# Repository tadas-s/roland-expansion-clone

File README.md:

# DIY Roland JV-1080 expansion card

Recently I restored a [Roland XP-60][1] synth for a friend. It's a digital sample
based synth with possibility of expanding sample set with up to 4 expansion
cards. And, while looking at service manual I got carried away a little...
Those expansion cards have a pretty straightforward interface - 8 bit data bus,
20 bit address bus, a few chip enable pins. Looked like something very DIYable.

Needless to say, I'm not the first one to notice it. Someone made copies of available
expansions and reverse engineered the format. [SRJV][3] is a script collection
to create/manipulate those ROMs.

# Schematic

For my own clone I used AM29F016D-70E4C flash chips. These are obsolete but still
widely available on eBay.

I included extra headers to expose flash WE, RESET for in-circuit programming,
but that part is untested - I ended up pre-programming chips before soldering.

# PCB

Did not want to spend too much time on layout so went with a more expensive
4 layer board.

# Assembled board

Two expansions installed next to one original from Roland:

[1]: https://www.vintagesynth.com/roland/xp-60
[2]: https://en.wikipedia.org/wiki/Roland_JV-1080
[3]: https://github.com/PythonBlue/SRJV

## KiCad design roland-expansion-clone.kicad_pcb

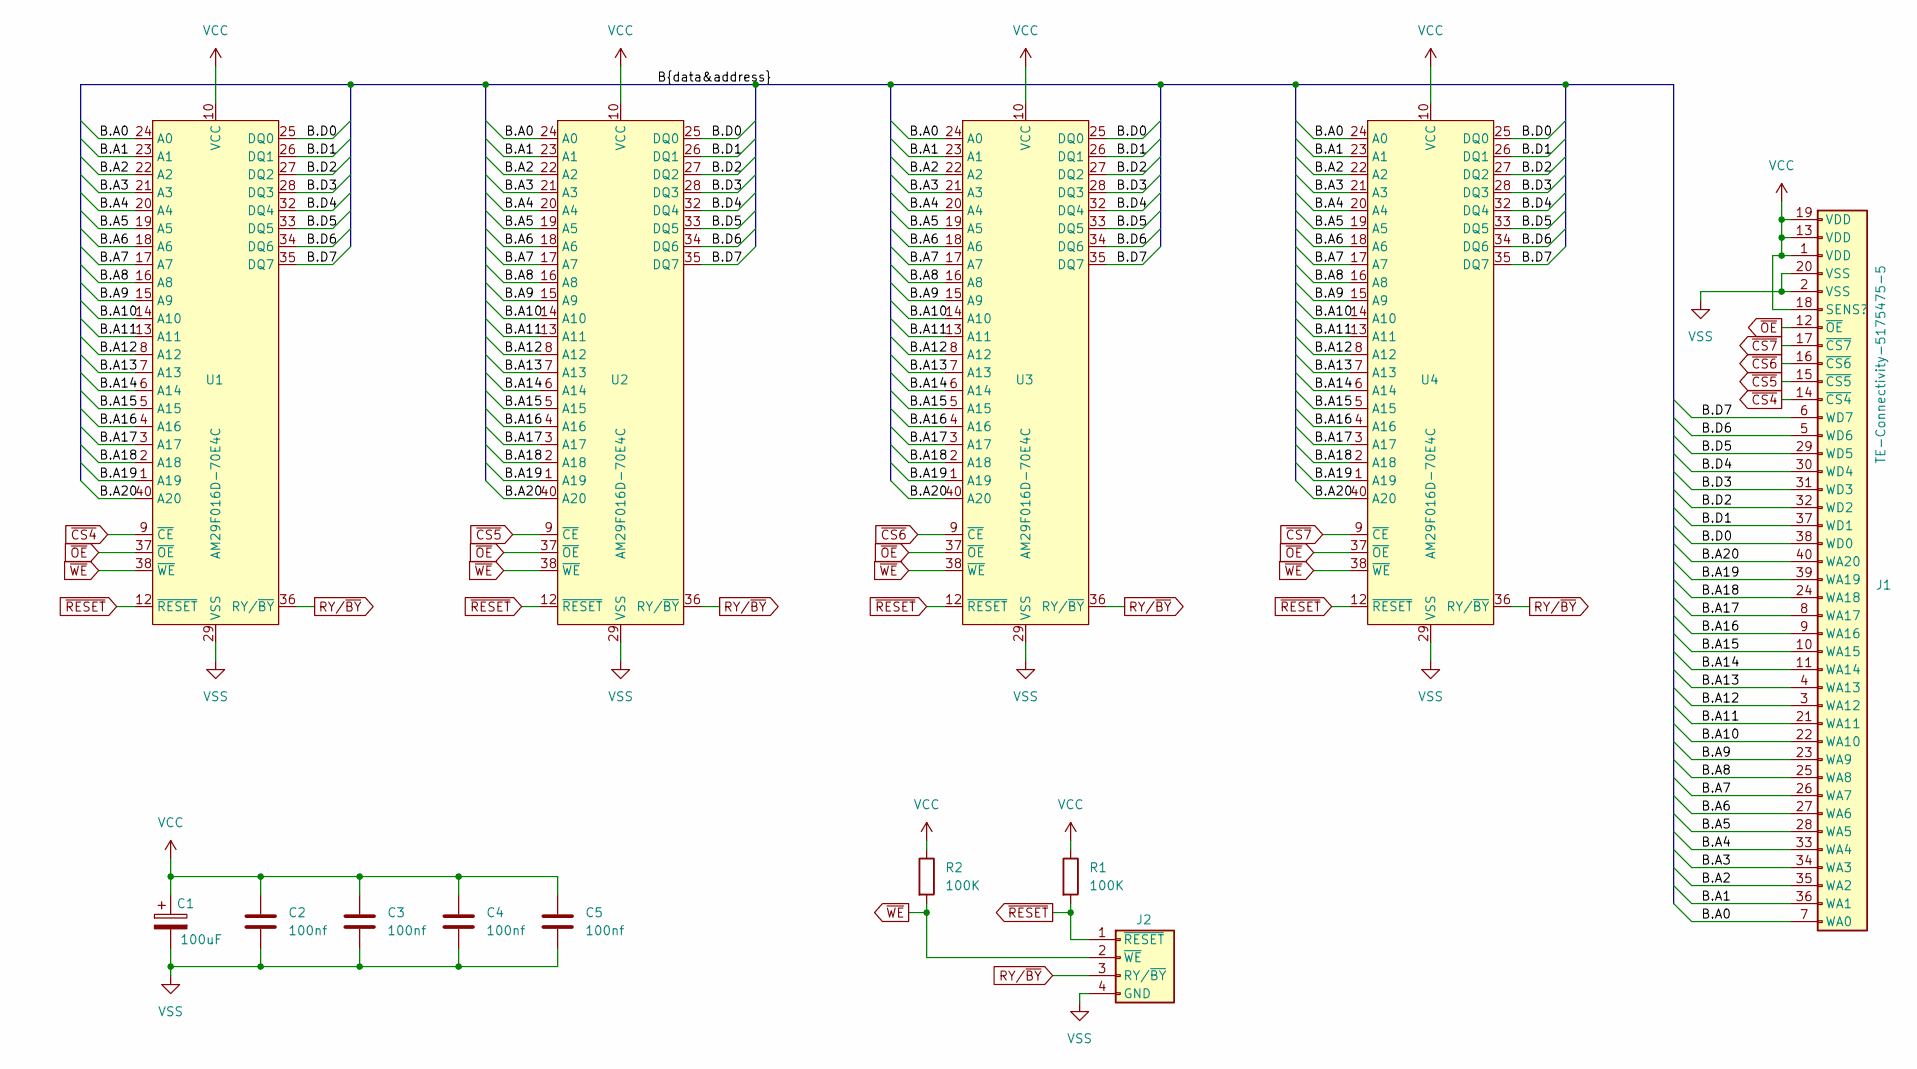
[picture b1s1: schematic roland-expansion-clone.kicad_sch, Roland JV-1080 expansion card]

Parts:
C1: 100uF; CP_Elec_6.3x5.7
C2, C3, C4, C5: 100nf; C_0603_1608Metric_Pad1.08x0.95mm_HandSolder
J1: TE-Connectivity-5175475-5
J2: Conn_01x04; PinHeader_1x04_P2.54mm_Horizontal
R1, R2: 100K; R_1206_3216Metric_Pad1.30x1.75mm_HandSolder
U1, U2, U3, U4: AM29F016D-70E4C; TSOP-I-40_18.4x10mm_P0.5mm

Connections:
/B.A0: J1.7 (WA0), U1.24 (A0), U2.24 (A0), U3.24 (A0), U4.24 (A0)
/B.A1: J1.36 (WA1), U1.23 (A1), U2.23 (A1), U3.23 (A1), U4.23 (A1)
/B.A2: J1.35 (WA2), U1.22 (A2), U2.22 (A2), U3.22 (A2), U4.22 (A2)
/B.A3: J1.34 (WA3), U1.21 (A3), U2.21 (A3), U3.21 (A3), U4.21 (A3)
/B.A4: J1.33 (WA4), U1.20 (A4), U2.20 (A4), U3.20 (A4), U4.20 (A4)
/B.A5: J1.28 (WA5), U1.19 (A5), U2.19 (A5), U3.19 (A5), U4.19 (A5)
/B.A6: J1.27 (WA6), U1.18 (A6), U2.18 (A6), U3.18 (A6), U4.18 (A6)
/B.A7: J1.26 (WA7), U1.17 (A7), U2.17 (A7), U3.17 (A7), U4.17 (A7)
/B.A8: J1.25 (WA8), U1.16 (A8), U2.16 (A8), U3.16 (A8), U4.16 (A8)
/B.A9: J1.23 (WA9), U1.15 (A9), U2.15 (A9), U3.15 (A9), U4.15 (A9)
/B.A10: J1.22 (WA10), U1.14 (A10), U2.14 (A10), U3.14 (A10), U4.14 (A10)
/B.A11: J1.21 (WA11), U1.13 (A11), U2.13 (A11), U3.13 (A11), U4.13 (A11)
/B.A12: J1.3 (WA12), U1.8 (A12), U2.8 (A12), U3.8 (A12), U4.8 (A12)
/B.A13: J1.4 (WA13), U1.7 (A13), U2.7 (A13), U3.7 (A13), U4.7 (A13)
/B.A14: J1.11 (WA14), U1.6 (A14), U2.6 (A14), U3.6 (A14), U4.6 (A14)
/B.A15: J1.10 (WA15), U1.5 (A15), U2.5 (A15), U3.5 (A15), U4.5 (A15)
/B.A16: J1.9 (WA16), U1.4 (A16), U2.4 (A16), U3.4 (A16), U4.4 (A16)
/B.A17: J1.8 (WA17), U1.3 (A17), U2.3 (A17), U3.3 (A17), U4.3 (A17)
/B.A18: J1.24 (WA18), U1.2 (A18), U2.2 (A18), U3.2 (A18), U4.2 (A18)
/B.A19: J1.39 (WA19), U1.1 (A19), U2.1 (A19), U3.1 (A19), U4.1 (A19)
/B.A20: J1.40 (WA20), U1.40 (A20), U2.40 (A20), U3.40 (A20), U4.40 (A20)
/B.D0: J1.38 (WD0), U1.25 (DQ0), U2.25 (DQ0), U3.25 (DQ0), U4.25 (DQ0)
/B.D1: J1.37 (WD1), U1.26 (DQ1), U2.26 (DQ1), U3.26 (DQ1), U4.26 (DQ1)
/B.D2: J1.32 (WD2), U1.27 (DQ2), U2.27 (DQ2), U3.27 (DQ2), U4.27 (DQ2)
/B.D3: J1.31 (WD3), U1.28 (DQ3), U2.28 (DQ3), U3.28 (DQ3), U4.28 (DQ3)
/B.D4: J1.30 (WD4), U1.32 (DQ4), U2.32 (DQ4), U3.32 (DQ4), U4.32 (DQ4)
/B.D5: J1.29 (WD5), U1.33 (DQ5), U2.33 (DQ5), U3.33 (DQ5), U4.33 (DQ5)
/B.D6: J1.5 (WD6), U1.34 (DQ6), U2.34 (DQ6), U3.34 (DQ6), U4.34 (DQ6)
/B.D7: J1.6 (WD7), U1.35 (DQ7), U2.35 (DQ7), U3.35 (DQ7), U4.35 (DQ7)
RY/~BY: J2.3 (RY/~BY), U1.36 (RY/~BY), U2.36 (RY/~BY), U3.36 (RY/~BY), U4.36 (RY/~BY)
VCC: C1.1, C2.1, C3.1, C4.1, C5.1, J1.1 (VDD), J1.13 (VDD), J1.18 (SENS?), J1.19 (VDD), R1.1, R2.1, U1.10 (VCC), U1.31 (VCC), U2.10 (VCC), U2.31 (VCC), U3.10 (VCC), U3.31 (VCC), U4.10 (VCC), U4.31 (VCC)
VSS: C1.2, C2.2, C3.2, C4.2, C5.2, J1.2 (VSS), J1.20 (VSS), J2.4 (GND), U1.29 (VSS), U1.30 (VSS), U2.29 (VSS), U2.30 (VSS), U3.29 (VSS), U3.30 (VSS), U4.29 (VSS), U4.30 (VSS)
~CS4: J1.14 (~CS4), U1.9 (~CE)
~CS5: J1.15 (~CS5), U2.9 (~CE)
~CS6: J1.16 (~CS6), U3.9 (~CE)
~CS7: J1.17 (~CS7), U4.9 (~CE)
~OE: J1.12 (~OE), U1.37 (~OE), U2.37 (~OE), U3.37 (~OE), U4.37 (~OE)
~RESET: J2.1 (~RESET), R1.2, U1.12 (~RESET), U2.12 (~RESET), U3.12 (~RESET), U4.12 (~RESET)
~WE: J2.2 (~WE), R2.2, U1.38 (~WE), U2.38 (~WE), U3.38 (~WE), U4.38 (~WE)

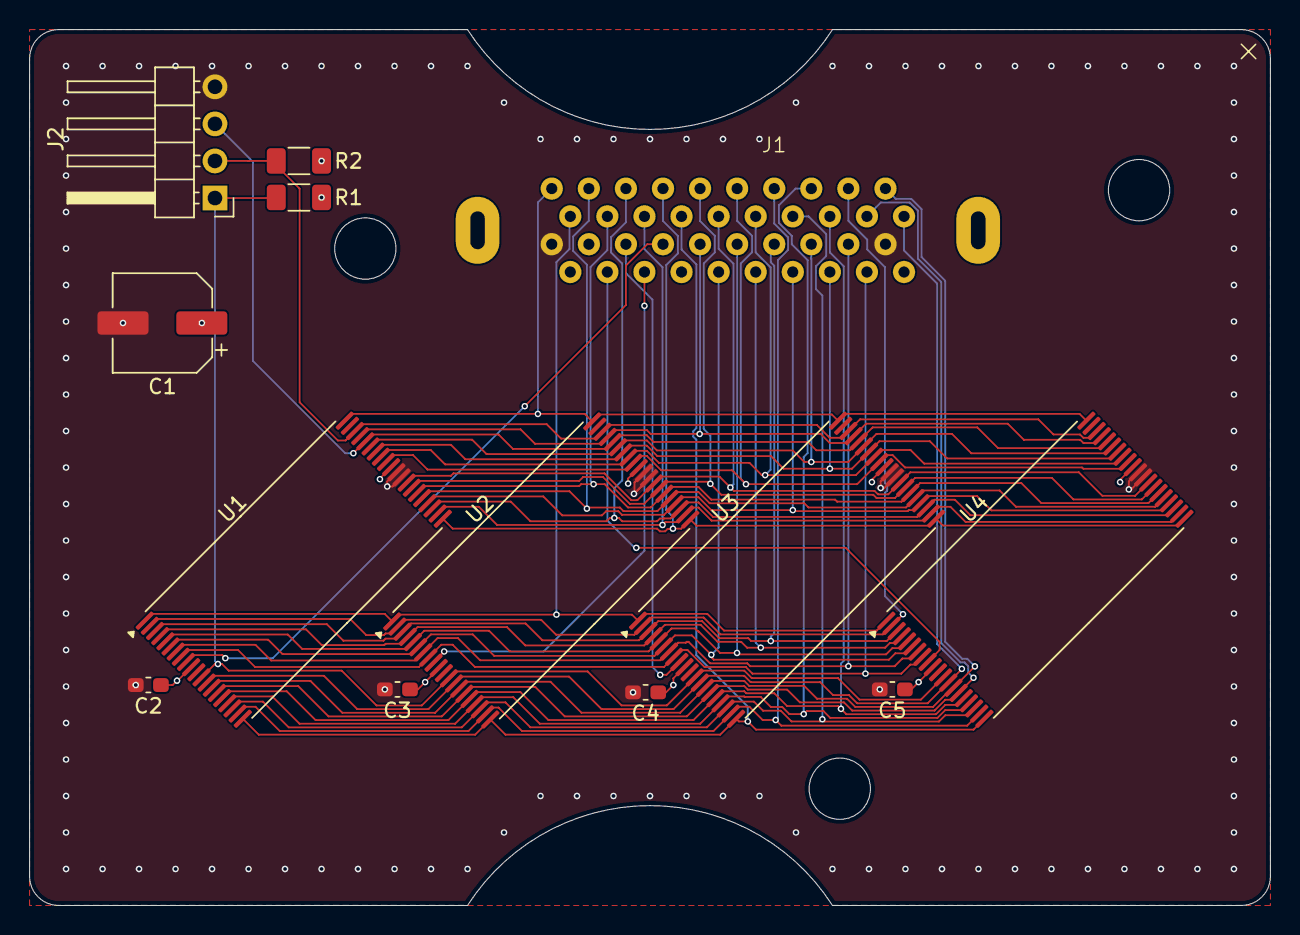
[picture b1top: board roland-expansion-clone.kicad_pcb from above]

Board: 4 copper layers, 85.0 x 60.0 mm, 13 parts (0 on the bottom side), 39 nets.

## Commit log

2026-03-24 First working revision
    Manufactured by aisler.net, assembled and tested with Roland XP-60.
2026-03-24 README.md and more for context
